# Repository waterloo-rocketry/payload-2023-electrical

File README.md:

WELCOME TO PAYLOAD: "NOT QUITE DEPLOYABLE"

Here is the folder in the google drive where most of our research happens (if you don't have access, and need it, ask!)
https://drive.google.com/drive/folders/1Cd6_AShmbkWPmAZkzhvAZI7hbHMKju_5?usp=sharing

If you can't find the project you're looking for, make sure to check the branches

CONFLUENCE (but don't expect it to be updated)
https://uwaterloo.atlassian.net/wiki/spaces/ROCKETRY/pages/42574873580/Payload

**How to Start Editing Schematics**
- Clone the "canhw" repo from https://github.com/waterloo-rocketry/canhw
- Enter canhw and make sure you are on the most up to date version of master branch
- Make sure that both the payload-2023-electrical and canhw repos are in the same parent directory! KiCAD will not be able to find our custom libraries otherwise

# 2023 Electrical Overview
Please see the updated .drawio file, which contains a detailed electrical block diagram

The 2023 electrical system is made up of 5 boards:

### GPS board
- Can be found at https://github.com/waterloo-rocketry/canhw/tree/master/gps
- GPS is a very simple board. It gets data from a GPS reciever and forwards it over CAN. 
- Data from GPS board will be the x/y position measurement input to state estimation
- A copy will be mounted on GrandPapa

### Logger board
- Can be found at https://github.com/waterloo-rocketry/canhw/tree/master/logger
- Logger is also a very simple board. It reads in all the CAN messages it sees and saves them to an SD card
- Logger is extremely useful for all sorts of diagnostics, but will allow us to collect all the sensor data as the rocket flies, do some post-flight analysis, and hopefully figure out if state estimation did a good job
- A copy will be mounted on GrandPapa

### Minisensor
- Can be found at https://github.com/waterloo-rocketry/canhw/tree/master/sensor_mini 
- Minisensor gets data from an altimeter, IMU (an accelerometer, magnetometer, and gyroscope packed into one chip) and optionally one or more pressure transmitters, RTDs, strain gauges, the list goes on (there are some generic amplifier circuits that have a variety of uses).
- For its application to payload, we only care about the IMU and altimeter, which provide most of the data to state estimation
- Will be wired to GrandPapa to maximize flexibility and because there's no more space on it lol

### COTS PIC Dev Board (DM320209)
- Datasheet can be found at http://ww1.microchip.com/downloads/en/DeviceDoc/Curiosity_PIC32MZEF2.0_Development_Board_Users_Guide_DS70005400A.pdf
- This beefy boy runs state estimation cause we did not have time to design a second board from scratch and matrix multiplication (which is basically what state estimation is) is really computationally intensive. An NVIDIA GeForce RTX 4090 GPU was proposed as an alternative but was ultimately struck down because "it would cost double payload's yearly budget" and "doesn't obey the 3U Cubesat standard".

### GrandPapa
- Can be found RIGHT HERE under "/GrandPapa_Board"
- GrandPapa is our power management, battery charging, and communications board. It pulls from the rocket to power the payload's systems, and pulls from the payload's battery supply when external power is no longer available. It also manages communication between RocketCAN (the rocket's main communication network) and the payload's internal network. Because CAN is a broadcast protocol (every board sees every message on the network all the time), and payload will be constantly transmitting sensor data, we do not want those messages interfering with whatever is happening on RocketCAN or vice versa
- See the schamtic notes for details on the power path

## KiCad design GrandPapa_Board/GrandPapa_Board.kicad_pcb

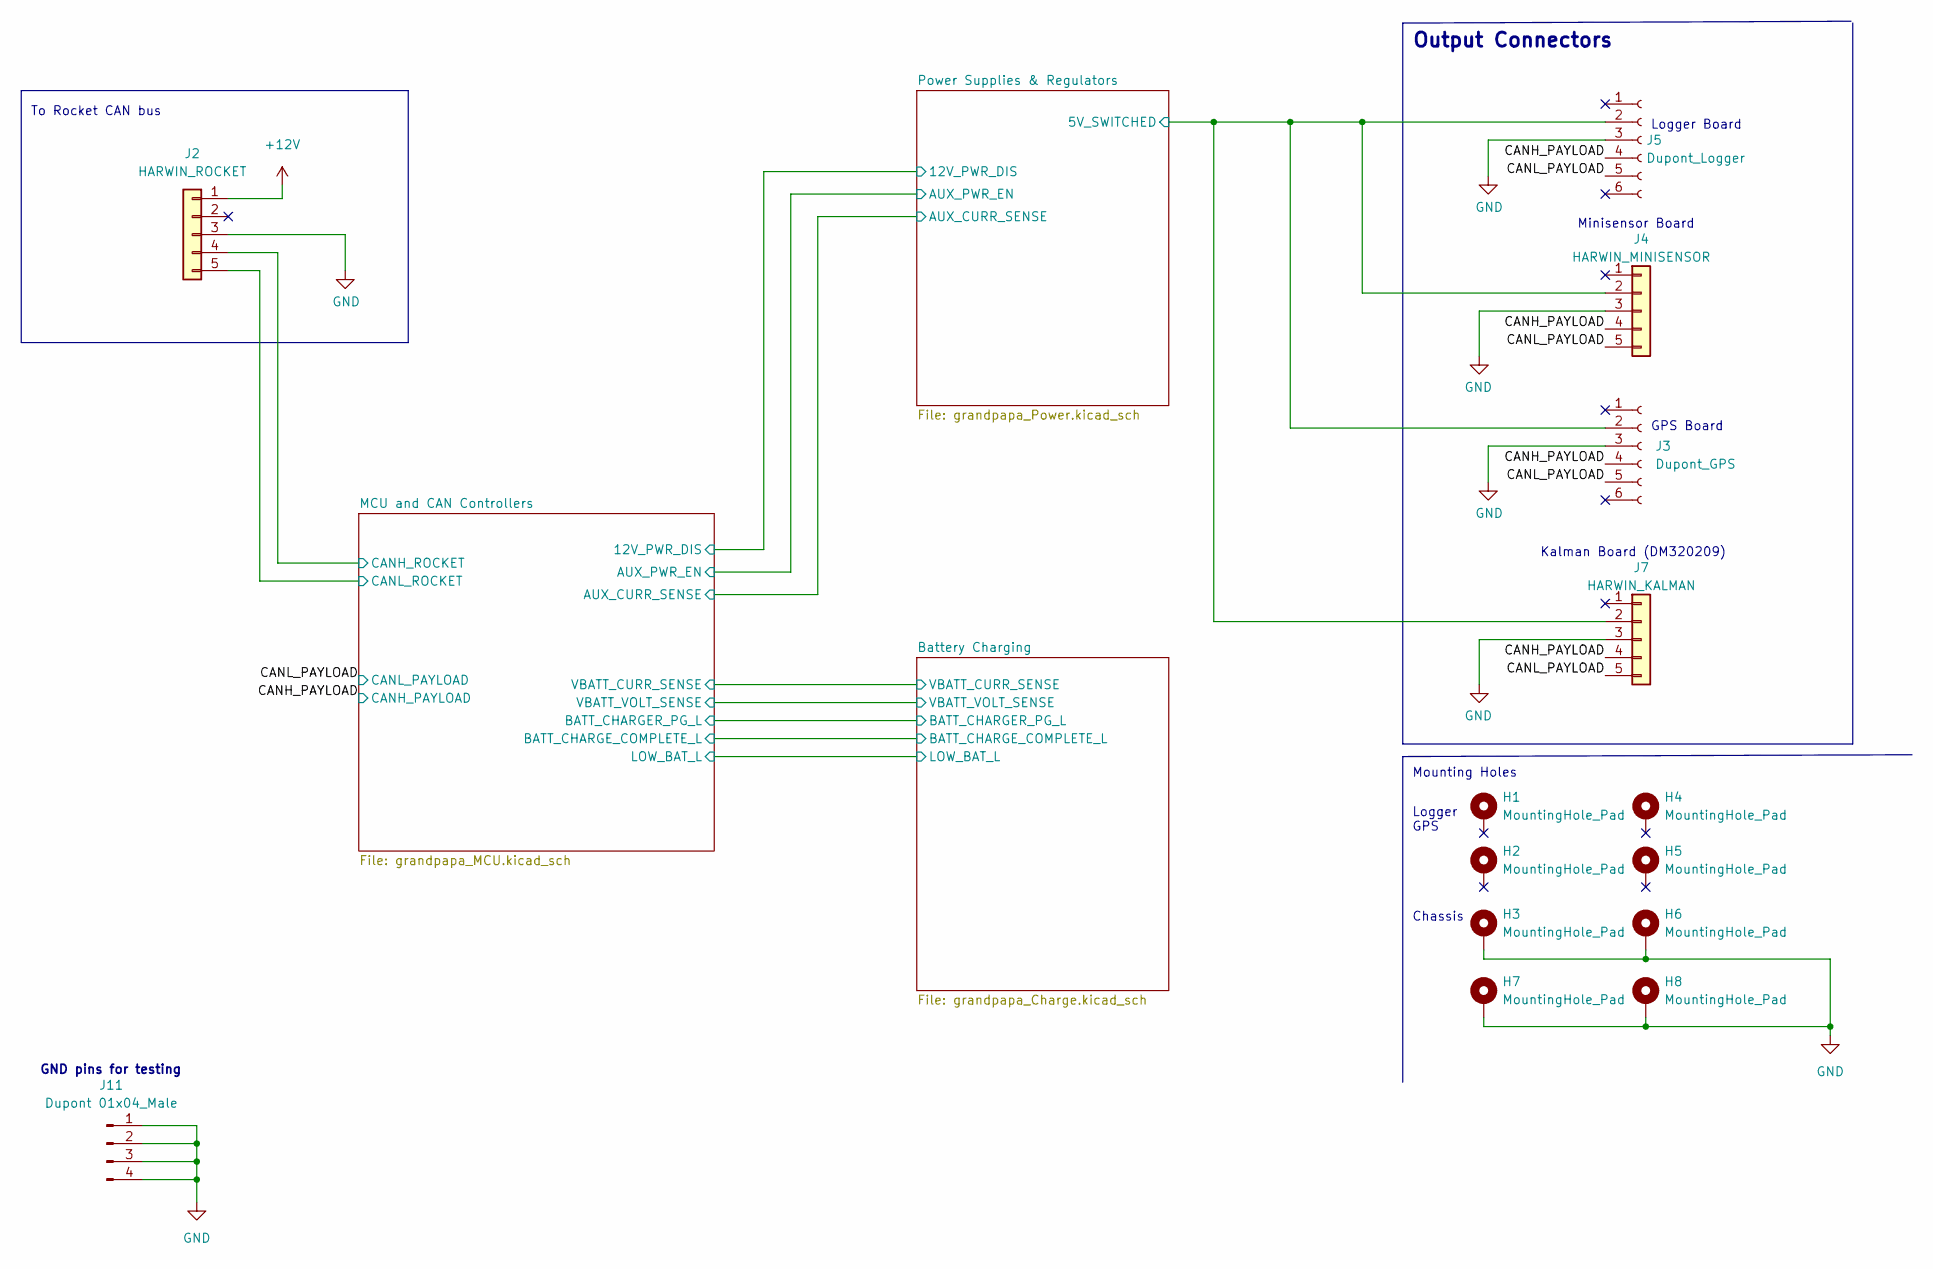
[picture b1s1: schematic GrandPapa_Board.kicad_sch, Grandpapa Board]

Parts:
H1, H2, H4, H5: MountingHole_Pad; MountingHole_3.2mm_M3_Pad
H3, H6, H7, H8: MountingHole_Pad; MountingHole_3.5mm_Pad_Via
J2: HARWIN_ROCKET; connector_Harwin_M80-5000642
J3: Dupont_GPS; connector_Harwin_M80-5000642
J4: HARWIN_MINISENSOR; connector_Harwin_M80-5000642
J5: Dupont_Logger; connector_Harwin_M80-5000642
J7: HARWIN_KALMAN; connector_Harwin_M80-5000642
J11: Dupont 01x04_Male; PinHeader_1x04_P2.54mm_Vertical

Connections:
+12V: J2.1; also elsewhere on the board
/CANH_PAYLOAD: J3.4, J4.4, J5.4, J7.4; also elsewhere on the board
/CANL_PAYLOAD: J3.5, J4.5, J5.5, J7.5; also elsewhere on the board
/MCU and CAN Controllers/CANH_ROCKET: J2.4; also elsewhere on the board
/MCU and CAN Controllers/CANL_ROCKET: J2.5; also elsewhere on the board
/Power Supplies & Regulators/5V_SWITCHED: J3.2, J4.2, J5.2, J7.2; also elsewhere on the board
GND: H3.1, H6.1, H7.1, H8.1, J2.3, J3.3, J4.3, J5.3, J7.3, J11.1, J11.2, J11.3, J11.4; also elsewhere on the board

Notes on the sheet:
Logger Board
Kalman Board (DM320209)
GPS Board
Mounting Holes
Output Connectors
Minisensor Board
Chassis
To Rocket CAN bus
GND pins for testing
Logger GPS

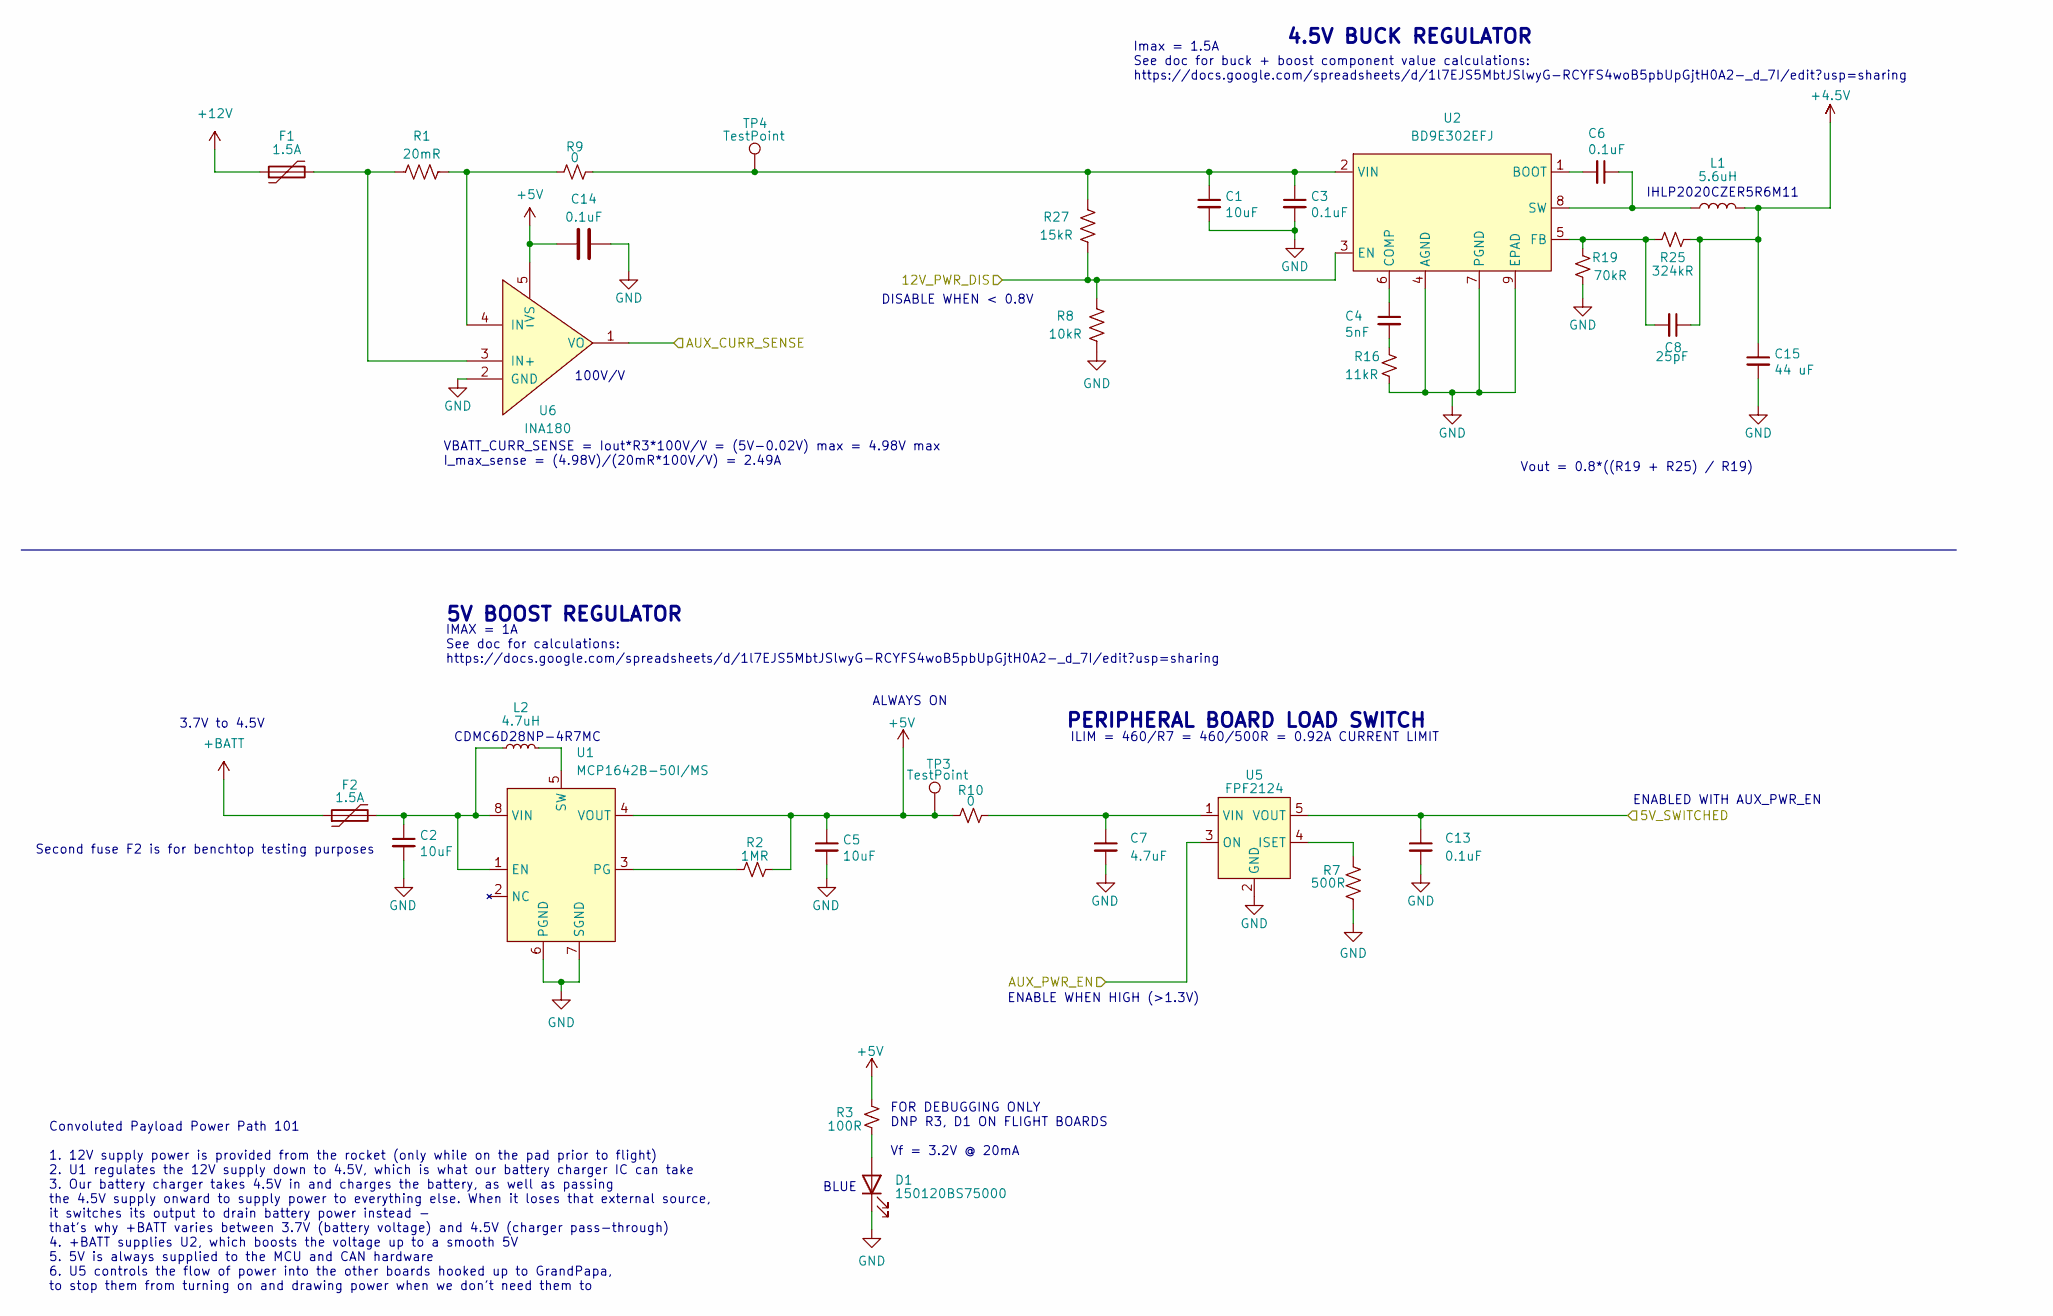
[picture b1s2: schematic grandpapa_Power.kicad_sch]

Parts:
C1, C2, C5: 10uF; C_0805_2012Metric_Pad1.18x1.45mm_HandSolder
C3, C6, C13, C14: 0.1uF; C_0805_2012Metric_Pad1.18x1.45mm_HandSolder
C4: 5nF; C_0805_2012Metric_Pad1.18x1.45mm_HandSolder
C7: 4.7uF; C_0805_2012Metric_Pad1.18x1.45mm_HandSolder
C8: 25pF; C_0805_2012Metric_Pad1.18x1.45mm_HandSolder
C15: 44 uF; C_0805_2012Metric_Pad1.18x1.45mm_HandSolder
D1: 150120BS75000; LED_1206_3216Metric_Pad1.42x1.75mm_HandSolder
F1, F2: 1.5A; Fuse_1812_4532Metric_Pad1.30x3.40mm_HandSolder
L1: 5.6uH; L_Vishay_IHLP-2020
L2: 4.7uH; L_Sumida_CDMC6D28_7.25x6.5mm
R1: 20mR; R_1206_3216Metric_Pad1.30x1.75mm_HandSolder
R2: 1MR; R_0805_2012Metric_Pad1.20x1.40mm_HandSolder
R3: 100R; R_0805_2012Metric_Pad1.20x1.40mm_HandSolder
R7: 500R; R_0805_2012Metric_Pad1.20x1.40mm_HandSolder
R8: 10kR; R_0805_2012Metric_Pad1.20x1.40mm_HandSolder
R9, R10: 0; R_0805_2012Metric_Pad1.20x1.40mm_HandSolder
R16: 11kR; R_0805_2012Metric_Pad1.20x1.40mm_HandSolder
R19: 70kR; R_0805_2012Metric_Pad1.20x1.40mm_HandSolder
R25: 324kR; R_0805_2012Metric_Pad1.20x1.40mm_HandSolder
R27: 15kR; R_0805_2012Metric_Pad1.20x1.40mm_HandSolder
TP3, TP4: TestPoint; PinHeader_1x01_P2.54mm_Vertical
U1: MCP1642B-50I/MS; MSOP-8_3x3mm_P0.65mm
U2: BD9E302EFJ; HTSOP-8-1EP_3.9x4.9mm_P1.27mm_EP2.4x3.2mm
U5: FPF2124; SOT-23-5_HandSoldering
U6: INA180; SOT-23-5_HandSoldering

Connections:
+4.5V: C8.1, C15.1, L1.2, R25.2; also elsewhere on the board
+5V: C5.1, C14.2, R2.1, R3.2, R10.1, TP3.1, U1.4 (VOUT), U6.5 (VS); also elsewhere on the board
+12V: F1.1; also elsewhere on the board
+BATT: F2.1; also elsewhere on the board
/MCU and CAN Controllers/12V_PWR_DIS: R8.1, R27.2, U2.3 (EN); also elsewhere on the board
/MCU and CAN Controllers/AUX_CURR_SENSE: U6.1 (VO); also elsewhere on the board
/MCU and CAN Controllers/AUX_PWR_EN: U5.3 (ON); also elsewhere on the board
/Power Supplies & Regulators/5V_SWITCHED: C13.1, U5.5 (VOUT); also elsewhere on the board
GND: C1.2, C2.2, C3.2, C5.2, C7.2, C13.2, C14.1, C15.2, D1.1 (K), R7.2, R8.2, R16.1, R19.2, U1.6 (PGND), U1.7 (SGND), U2.4 (AGND), U2.7 (PGND), U2.9 (EPAD), U5.2 (GND), U6.2 (GND); also elsewhere on the board
unnamed: C1.1, C3.1, R9.2, R27.1, TP4.1, U2.2 (VIN)
unnamed: C2.1, F2.2, L2.1, U1.1 (EN), U1.8 (VIN)
unnamed: C4.1, U2.6 (COMP)
unnamed: C4.2, R16.2
unnamed: C6.1, L1.1, U2.8 (SW)
unnamed: C6.2, U2.1 (BOOT)
unnamed: C7.1, R10.2, U5.1 (VIN)
unnamed: C8.2, R19.1, R25.1, U2.5 (FB)
unnamed: D1.2 (A), R3.1
unnamed: F1.2, R1.2, U6.3 (IN+)
unnamed: L2.2, U1.5 (SW)
unnamed: R1.1, R9.1, U6.4 (IN-)
unnamed: R2.2, U1.3 (PG)
unnamed: R7.1, U5.4 (ISET)

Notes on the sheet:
ILIM = 460/R7 = 460/500R = 0.92A CURRENT LIMIT
DISABLE WHEN < 0.8V
5V BOOST REGULATOR
4.5V BUCK REGULATOR
ALWAYS ON
PERIPHERAL BOARD LOAD SWITCH
BLUE
Vout = 0.8*((R19 + R25) / R19)
100V/V
3.7V to 4.5V
Imax = 1.5A See doc for buck + boost component value calculations: https://docs.google.com/spreadsheets/d/1l7EJS5MbtJSlwyG-RCYFS4woB5pbUpGjtH0A2-_d_7I/edit?usp=sharing
ENABLED WITH AUX_PWR_EN
FOR DEBUGGING ONLY DNP R3, D1 ON FLIGHT BOARDS Vf = 3.2V @ 20mA
VBATT_CURR_SENSE = Iout*R3*100V/V = (5V-0.02V) max = 4.98V max I_max_sense = (4.98V)/(20mR*100V/V) = 2.49A
ENABLE WHEN HIGH (>1.3V)
IHLP2020CZER5R6M11
CDMC6D28NP-4R7MC
IMAX = 1A See doc for calculations: https://docs.google.com/spreadsheets/d/1l7EJS5MbtJSlwyG-RCYFS4woB5pbUpGjtH0A2-_d_7I/edit?usp=sharing
Convoluted Payload Power Path 101 1. 12V supply power is provided from the rocket (only while on the pad prior to flight) 2. U1 regulates the 12V supply down to 4.5V, which is what our battery charger IC can take 3. Our battery charger takes 4.5V in and charges the battery, as well as passing the 4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
Second fuse F2 is for benchtop testing purposes

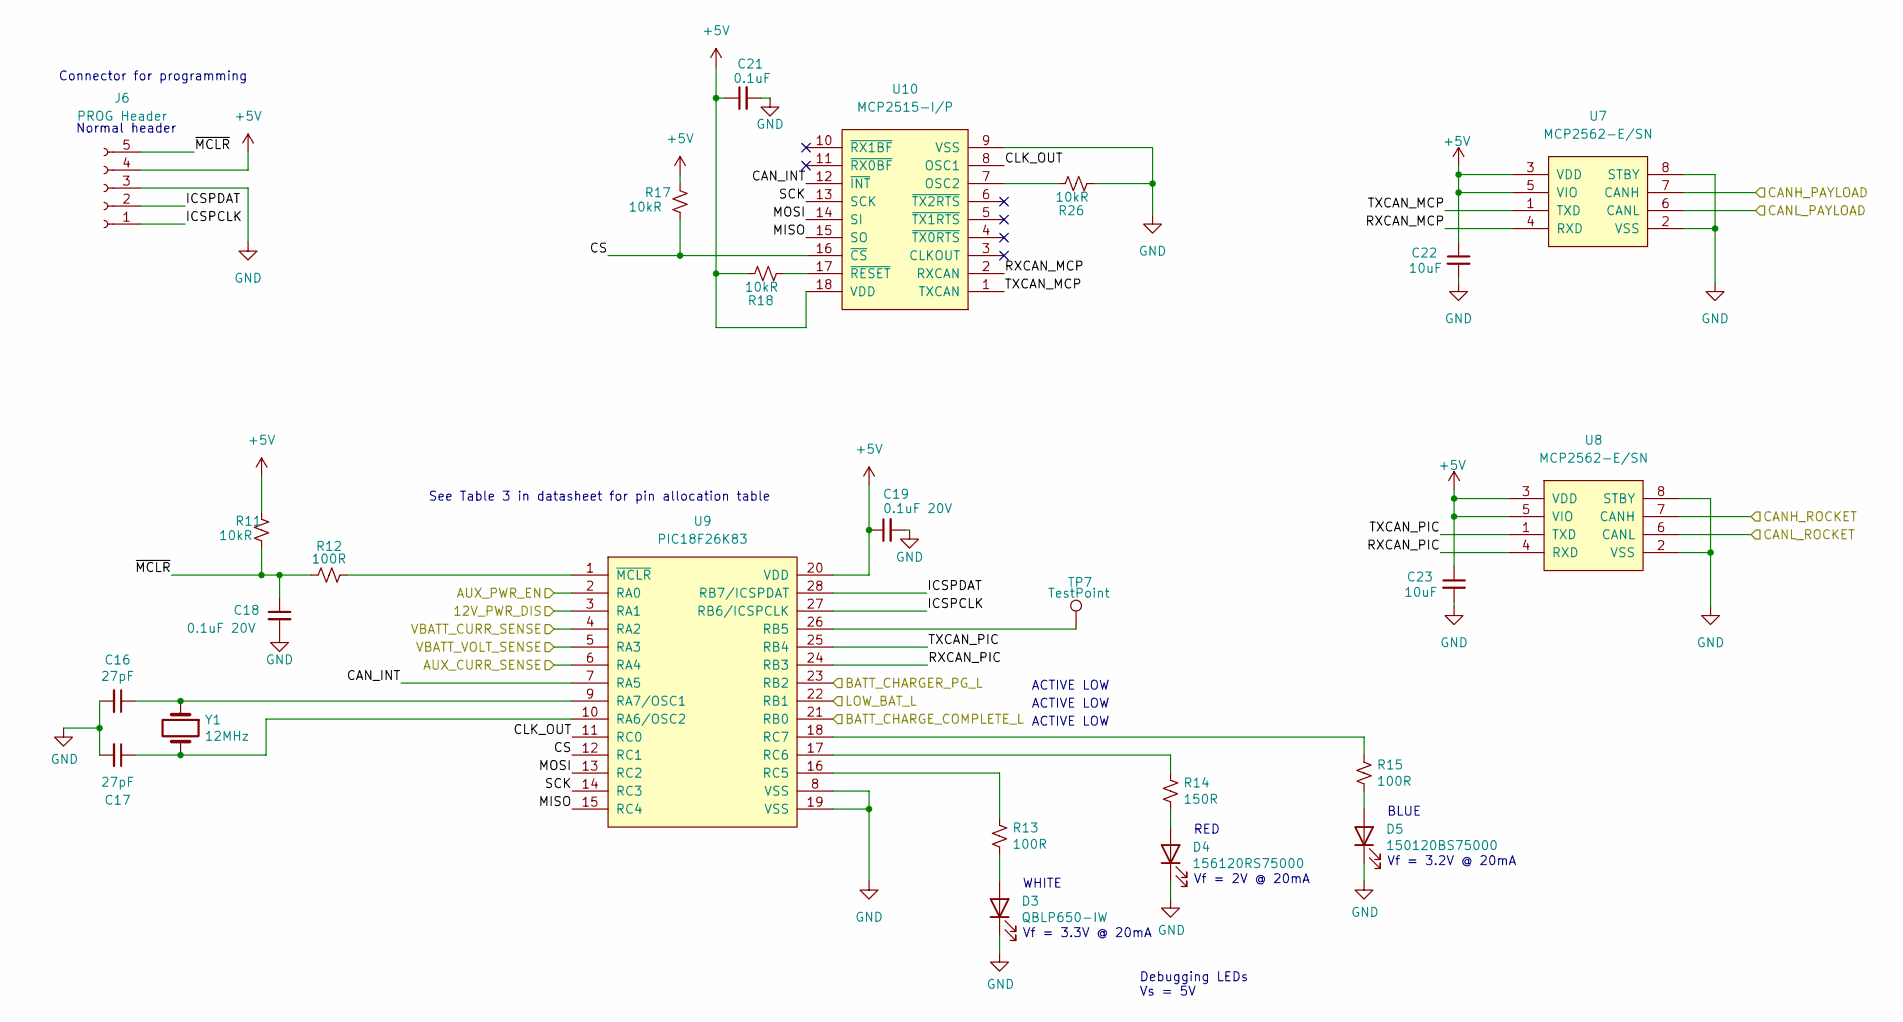
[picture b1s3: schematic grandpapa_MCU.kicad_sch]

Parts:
C16, C17: 27pF; C_0805_2012Metric_Pad1.18x1.45mm_HandSolder
C18, C19: 0.1uF 20V; C_0805_2012Metric_Pad1.18x1.45mm_HandSolder
C21: 0.1uF; C_0805_2012Metric_Pad1.18x1.45mm_HandSolder
C22, C23: 10uF; C_0805_2012Metric_Pad1.18x1.45mm_HandSolder
D3: QBLP650-IW; LED_1206_3216Metric_Pad1.42x1.75mm_HandSolder
D4: 156120RS75000; LED_1206_3216Metric_Pad1.42x1.75mm_HandSolder
D5: 150120BS75000; LED_1206_3216Metric_Pad1.42x1.75mm_HandSolder
J6: PROG Header; PinHeader_1x05_P2.54mm_Vertical
R11, R17, R18, R26: 10kR; R_0805_2012Metric_Pad1.20x1.40mm_HandSolder
R12, R13, R15: 100R; R_0805_2012Metric_Pad1.20x1.40mm_HandSolder
R14: 150R; R_0805_2012Metric_Pad1.20x1.40mm_HandSolder
TP7: TestPoint; PinHeader_1x01_P2.54mm_Vertical
U7, U8: MCP2562-E/SN; SOIC-8_3.9x4.9mm_P1.27mm
U9: PIC18F26K83; SSOP-28_5.3x10.2mm_P0.65mm
U10: MCP2515-I/P; SOIC-18W_7.5x11.6mm_P1.27mm
Y1: 12MHz; Crystal_HC49-4H_Vertical

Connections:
+5V: C19.1, C21.1, C22.1, C23.1, J6.4, R11.1, R17.1, R18.1, U7.3 (VDD), U7.5 (VIO), U8.3 (VDD), U8.5 (VIO), U9.20 (VDD), U10.18 (VDD); also elsewhere on the board
/Battery Charging/BATT_CHARGER_PG_L: U9.23 (RB2); also elsewhere on the board
/Battery Charging/BATT_CHARGE_COMPLETE_L: U9.21 (RB0); also elsewhere on the board
/Battery Charging/LOW_BAT_L: U9.22 (RB1); also elsewhere on the board
/Battery Charging/VBATT_CURR_SENSE: U9.4 (RA2); also elsewhere on the board
/Battery Charging/VBATT_VOLT_SENSE: U9.5 (RA3); also elsewhere on the board
/CANH_PAYLOAD: U7.7 (CANH); also elsewhere on the board
/CANL_PAYLOAD: U7.6 (CANL); also elsewhere on the board
/MCU and CAN Controllers/12V_PWR_DIS: U9.3 (RA1); also elsewhere on the board
/MCU and CAN Controllers/AUX_CURR_SENSE: U9.6 (RA4); also elsewhere on the board
/MCU and CAN Controllers/AUX_PWR_EN: U9.2 (RA0); also elsewhere on the board
/MCU and CAN Controllers/CANH_ROCKET: U8.7 (CANH); also elsewhere on the board
/MCU and CAN Controllers/CANL_ROCKET: U8.6 (CANL); also elsewhere on the board
/MCU and CAN Controllers/CAN_INT: U9.7 (RA5), U10.12 (~INT)
/MCU and CAN Controllers/CLK_OUT: U9.11 (RC0), U10.8 (OSC1)
/MCU and CAN Controllers/CS: R17.2, U9.12 (RC1), U10.16 (~CS)
/MCU and CAN Controllers/ICSPCLK: J6.1, U9.27 (RB6/ICSPCLK)
/MCU and CAN Controllers/ICSPDAT: J6.2, U9.28 (RB7/ICSPDAT)
/MCU and CAN Controllers/MISO: U9.15 (RC4), U10.15 (SO)
/MCU and CAN Controllers/MOSI: U9.13 (RC2), U10.14 (SI)
/MCU and CAN Controllers/RXCAN_MCP: U7.4 (RXD), U10.2 (RXCAN)
/MCU and CAN Controllers/RXCAN_PIC: U8.4 (RXD), U9.24 (RB3)
/MCU and CAN Controllers/SCK: U9.14 (RC3), U10.13 (SCK)
/MCU and CAN Controllers/TXCAN_MCP: U7.1 (TXD), U10.1 (TXCAN)
/MCU and CAN Controllers/TXCAN_PIC: U8.1 (TXD), U9.25 (RB4)
/MCU and CAN Controllers/~MCLR: C18.1, J6.5, R11.2, R12.1
GND: C16.2, C17.2, C18.2, C19.2, C21.2, C22.2, C23.2, D3.1 (K), D4.1 (K), D5.1 (K), J6.3, R26.2, U7.2 (VSS), U7.8 (STBY), U8.2 (VSS), U8.8 (STBY), U9.8 (VSS), U9.19 (VSS), U10.9 (VSS); also elsewhere on the board
unnamed: C16.1, U9.9 (RA7/OSC1), Y1.1
unnamed: C17.1, U9.10 (RA6/OSC2), Y1.2
unnamed: D3.2 (A), R13.2
unnamed: D4.2 (A), R14.2
unnamed: D5.2 (A), R15.2
unnamed: R12.2, U9.1 (~MCLR)
unnamed: R13.1, U9.16 (RC5)
unnamed: R14.1, U9.17 (RC6)
unnamed: R15.1, U9.18 (RC7)
unnamed: R18.2, U10.17 (~RESET)
unnamed: R26.1, U10.7 (OSC2)
unnamed: TP7.1, U9.26 (RB5)

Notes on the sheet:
Vf = 3.2V @ 20mA
Vf = 3.3V @ 20mA
ACTIVE LOW
See Table 3 in datasheet for pin allocation table
BLUE
RED
Vf = 2V @ 20mA
WHITE
Debugging LEDs Vs = 5V
Normal header
Connector for programming

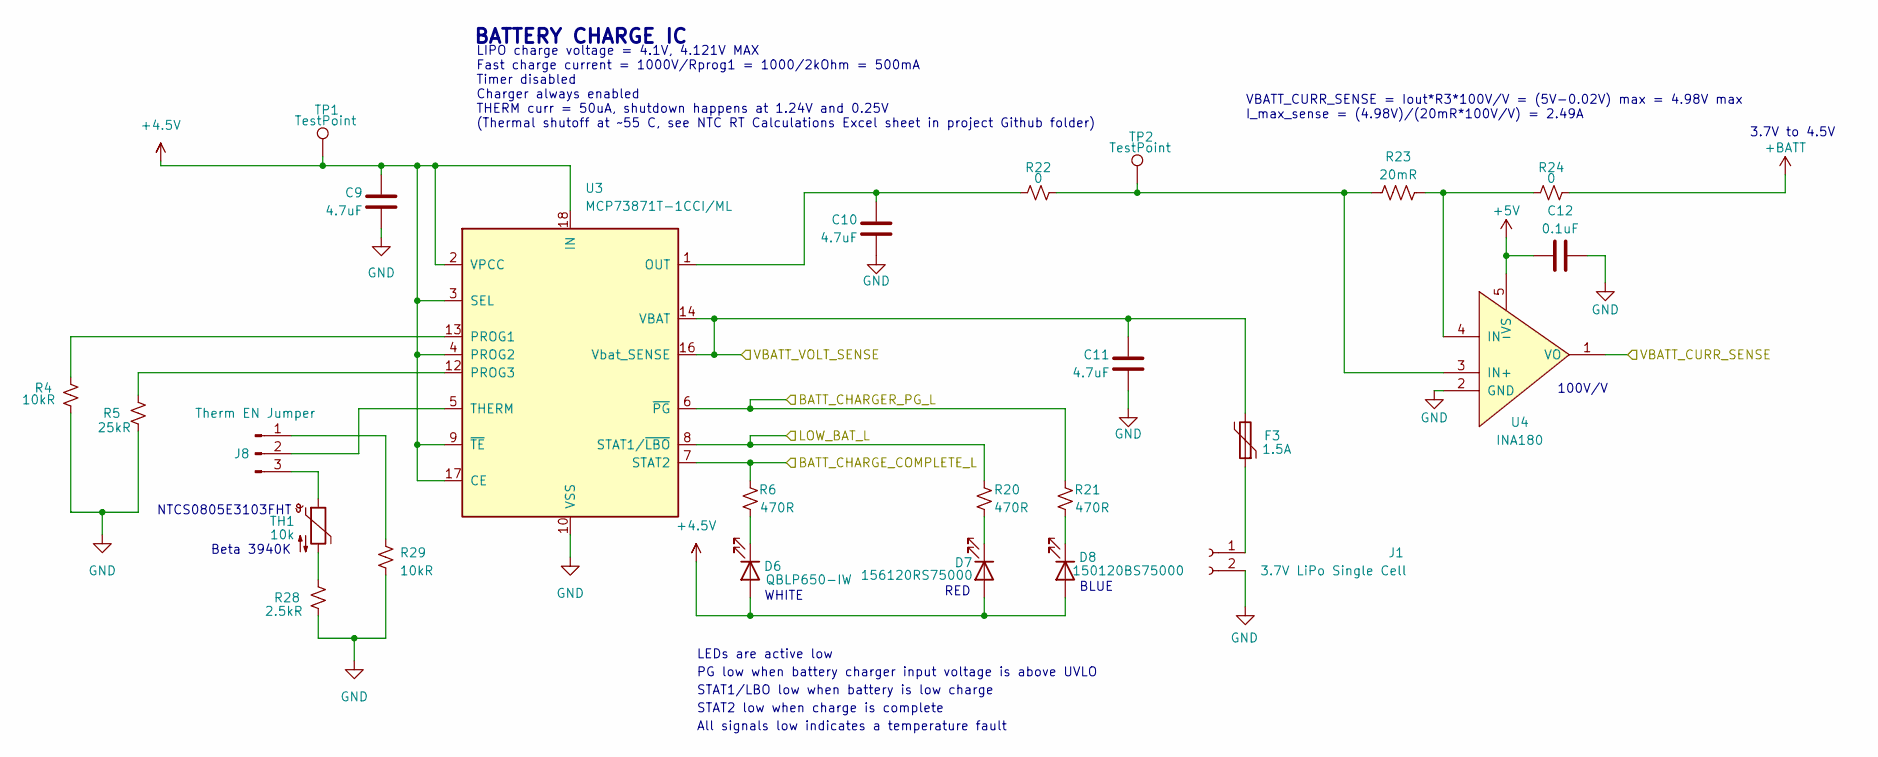
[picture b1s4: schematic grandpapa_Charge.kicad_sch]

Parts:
C9, C10, C11: 4.7uF; C_0805_2012Metric_Pad1.18x1.45mm_HandSolder
C12: 0.1uF; C_0805_2012Metric_Pad1.18x1.45mm_HandSolder
D6: QBLP650-IW; LED_1206_3216Metric_Pad1.42x1.75mm_HandSolder
D7: 156120RS75000; LED_1206_3216Metric_Pad1.42x1.75mm_HandSolder
D8: 150120BS75000; LED_1206_3216Metric_Pad1.42x1.75mm_HandSolder
F3: 1.5A; Fuse_1812_4532Metric_Pad1.30x3.40mm_HandSolder
J1: 3.7V LiPo Single Cell; JST_PH_S2B-PH-K_1x02_P2.00mm_Horizontal
J8: Therm EN Jumper; PinHeader_1x03_P2.54mm_Vertical
R4, R29: 10kR; R_0805_2012Metric_Pad1.20x1.40mm_HandSolder
R5: 25kR; R_0805_2012Metric_Pad1.20x1.40mm_HandSolder
R6, R20, R21: 470R; R_0805_2012Metric_Pad1.20x1.40mm_HandSolder
R22, R24: 0; R_0805_2012Metric_Pad1.20x1.40mm_HandSolder
R23: 20mR; R_1206_3216Metric_Pad1.30x1.75mm_HandSolder
R28: 2.5kR; R_0805_2012Metric_Pad1.20x1.40mm_HandSolder
TH1: 10k; R_0805_2012Metric_Pad1.20x1.40mm_HandSolder
TP1, TP2: TestPoint; PinHeader_1x01_P2.54mm_Vertical
U3: MCP73871T-1CCI/ML; QFN-20-1EP_4x4mm_P0.5mm_EP2.5x2.5mm
U4: INA180; SOT-23-5_HandSoldering

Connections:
+4.5V: C9.1, D6.2 (A), D7.2 (A), D8.2 (A), TP1.1, U3.2 (VPCC), U3.3 (SEL), U3.4 (PROG2), U3.9 (~TE), U3.17 (CE), U3.18 (IN), U3.19 (IN); also elsewhere on the board
+5V: C12.2, U4.5 (VS); also elsewhere on the board
+BATT: R24.2; also elsewhere on the board
/Battery Charging/BATT_CHARGER_PG_L: R21.2, U3.6 (~PG); also elsewhere on the board
/Battery Charging/BATT_CHARGE_COMPLETE_L: R6.2, U3.7 (STAT2); also elsewhere on the board
/Battery Charging/LOW_BAT_L: R20.1, U3.8 (STAT1/~LBO); also elsewhere on the board
/Battery Charging/VBATT_CURR_SENSE: U4.1 (VO); also elsewhere on the board
/Battery Charging/VBATT_VOLT_SENSE: C11.1, F3.2, U3.14 (VBAT), U3.15 (VBAT), U3.16 (Vbat_SENSE); also elsewhere on the board
GND: C9.2, C10.2, C11.2, C12.1, J1.2, R4.2, R5.2, R28.2, R29.2, U3.10 (VSS), U3.11 (VSS), U3.21 (VSS), U4.2 (GND); also elsewhere on the board
unnamed: C10.1, R22.1, U3.1 (OUT), U3.20 (OUT)
unnamed: D6.1 (K), R6.1
unnamed: D7.1 (K), R20.2
unnamed: D8.1 (K), R21.1
unnamed: F3.1, J1.1
unnamed: J8.1, R29.1
unnamed: J8.2, U3.5 (THERM)
unnamed: J8.3, TH1.1
unnamed: R4.1, U3.13 (PROG1)
unnamed: R5.1, U3.12 (PROG3)
unnamed: R22.2, R23.2, TP2.1, U4.3 (IN+)
unnamed: R23.1, R24.1, U4.4 (IN-)
unnamed: R28.1, TH1.2

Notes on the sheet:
BLUE
All signals low indicates a temperature fault
Beta 3940K
STAT1/LBO low when battery is low charge
100V/V
STAT2 low when charge is complete
LEDs are active low
3.7V to 4.5V
RED
NTCS0805E3103FHT
PG low when battery charger input voltage is above UVLO
BATTERY CHARGE IC
WHITE
LIPO charge voltage = 4.1V, 4.121V MAX Fast charge current = 1000V/Rprog1 = 1000/2kOhm = 500mA Timer disabled Charger always enabled THERM curr = 50uA, shutdown happens at 1.24V and 0.25V (Thermal shutoff at ~55 C, see NTC RT Calculations Excel sheet in project Github folder)
VBATT_CURR_SENSE = Iout*R3*100V/V = (5V-0.02V) max = 4.98V max I_max_sense = (4.98V)/(20mR*100V/V) = 2.49A
